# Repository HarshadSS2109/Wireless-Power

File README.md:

# Wireless-Power
A PCB design to implement Wireless power transfer using KiCAD

This wireless charging circuit is designed to power electronic devices with an output of up to 3.3V.
It utilizes an AC supply as the input, incorporating an overvoltage protection circuit to ensure safety. 
The output DC voltage is regulated using a voltage regulator, providing a stable and smooth direct current for the connected devices.

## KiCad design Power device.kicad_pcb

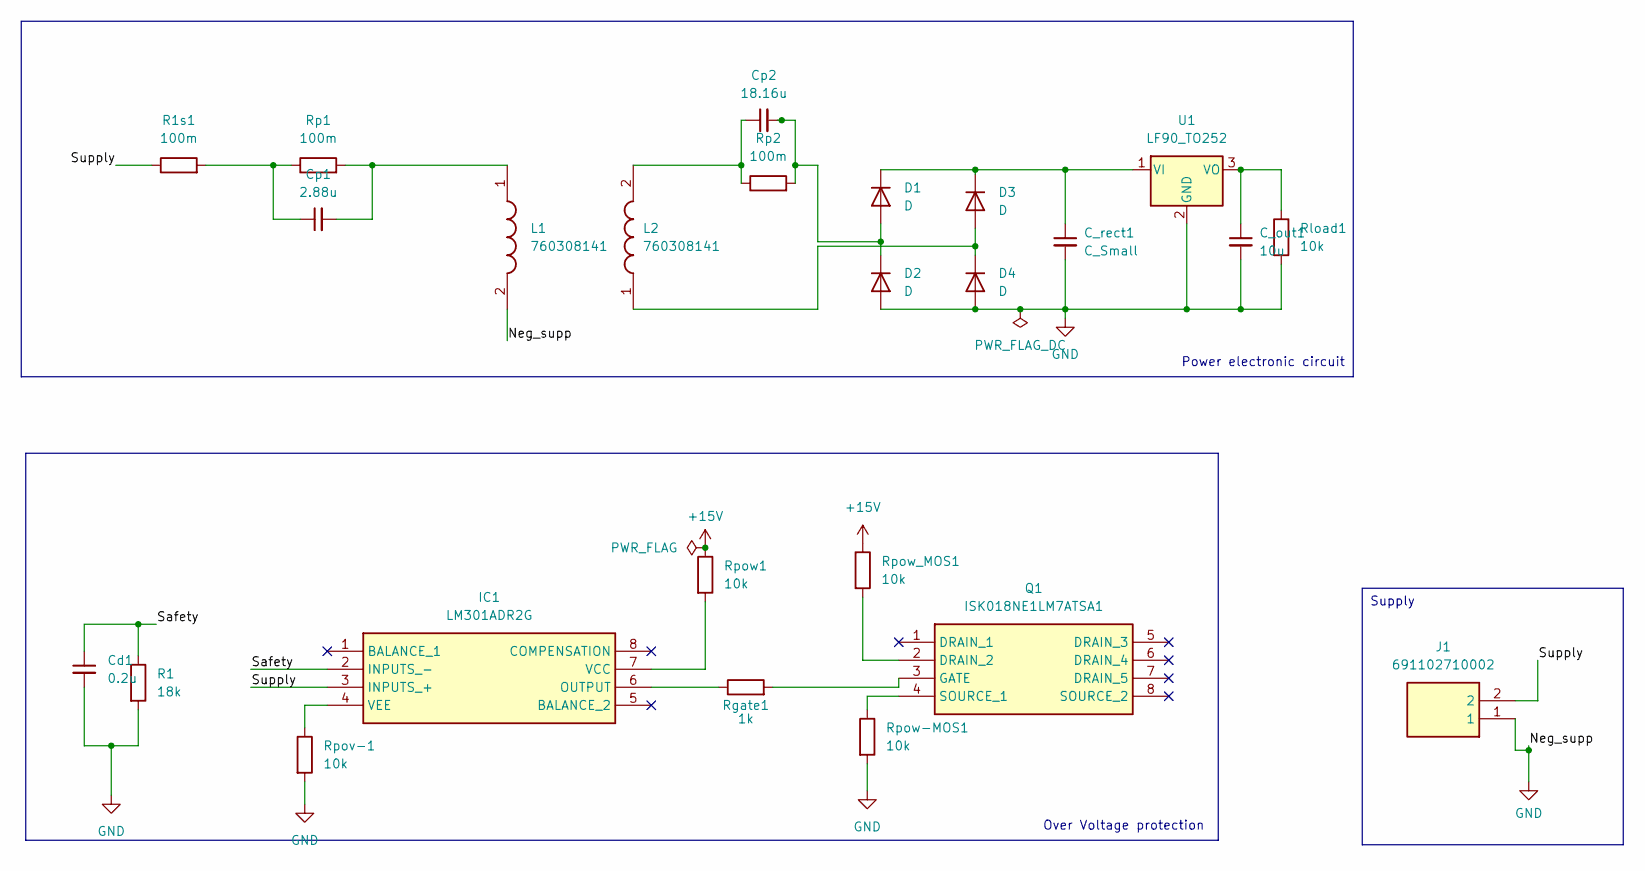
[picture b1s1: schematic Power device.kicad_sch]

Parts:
C_out1: 10u; C_0603_1608Metric_Pad1.08x0.95mm_HandSolder
C_rect1: C_Small; C_0402_1005Metric
Cd1: 0.2u; CAPC4532X220N
Cp1: 2.88u; CAPC4833X160N
Cp2: 18.16u; CAPC1005X56N
D1, D2, D3, D4: D; D_01005_0402Metric_Pad0.57x0.30mm_HandSolder
IC1: LM301ADR2G; SOIC127P600X175-8N; Mouser Part Number 863-LM301ADR2G
J1: 691102710002; SHDR2W100P0X500_1X2_1000X750X990P; Mouser Part Number 710-691102710002
L1, L2: 760308141; Mouser Part Number 710-760308141
Q1: ISK018NE1LM7ATSA1; Manufacturer_Part_Number ISK018NE1LM7ATSA1
R1: 18k; ERJB2__0612_
R1s1: 100m; ERJB2__0612_
Rgate1: 1k; ERJB2__0612_
Rload1: 10k; ERJB2__0612_
Rp1, Rp2: 100m; ERJB2__0612_
Rpov-1: 10k; ERJB2__0612_
Rpow1: 10k; ERJB2__0612_
Rpow-MOS1: 10k; ERJB2__0612_
Rpow_MOS1: 10k; ERJB2__0612_
U1: LF90_TO252; TO-252-2

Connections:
+15V: Rpow1.1, Rpow_MOS1.1
/Safety: Cd1.1, IC1.2 (INPUTS_-), R1.1
/Supply: IC1.3 (INPUTS_+), J1.2, R1s1.1
GND: C_out1.2, C_rect1.2, Cd1.2, D2.2 (A), D4.2 (A), J1.1, L1.2, R1.2, Rload1.2, Rpov-1.2, Rpow-MOS1.2, U1.2 (GND)
unnamed: Cp1.1, R1s1.2, Rp1.1
unnamed: Cp1.2, L1.1, Rp1.2
unnamed: Cp2.1, L2.2, Rp2.1
unnamed: Cp2.2, D1.2 (A), D2.1 (K), Rp2.2
unnamed: C_rect1.1, D1.1 (K), D3.1 (K), U1.1 (VI)
unnamed: D3.2 (A), D4.1 (K), L2.1
unnamed: IC1.6 (OUTPUT), Rgate1.1
unnamed: IC1.7 (VCC), Rpow1.2
unnamed: IC1.4 (VEE), Rpov-1.1
unnamed: Q1.2 (DRAIN_2), Rpow_MOS1.2
unnamed: Q1.3 (GATE), Rgate1.2
unnamed: Q1.4 (SOURCE_1), Rpow-MOS1.1
unnamed: C_out1.1, Rload1.1, U1.3 (VO)

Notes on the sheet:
Supply
Over Voltage protection
Power electronic circuit

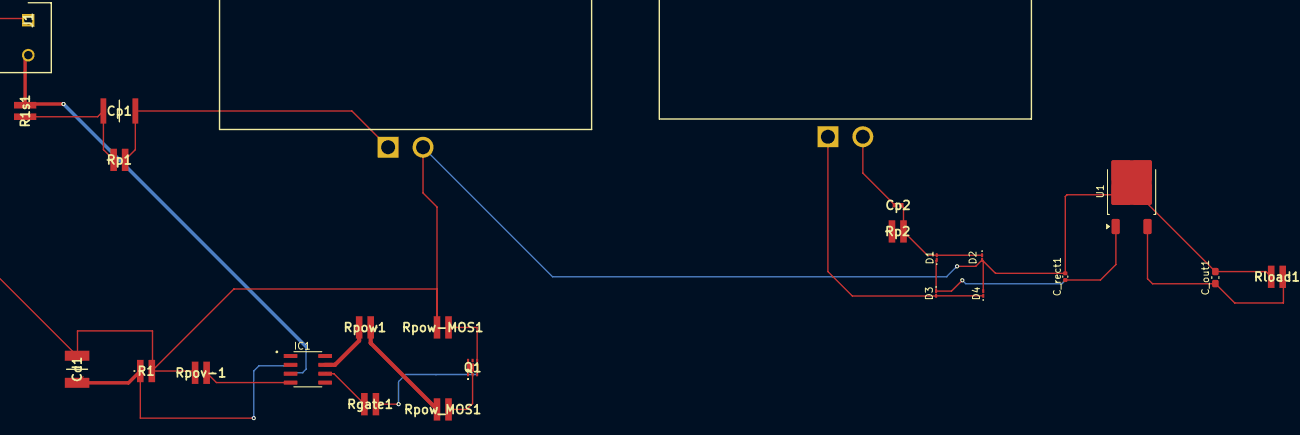
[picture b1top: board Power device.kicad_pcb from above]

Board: 2 copper layers, 25 parts (0 on the bottom side), 17 nets.

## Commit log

2025-01-26 Create temp
